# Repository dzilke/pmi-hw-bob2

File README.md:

# PMI backplane BreakOut Board for BreakOut Boards (BoB²)

This pcb is designed for the course PMI (Practical course Microcontroller
and Interface electronics) as a breakout board for right morpho connector
(CN10) of [STM32 Nucleo-64 boards](https://www.st.com/en/evaluation-tools/stm32-nucleo-boards.html). It distributes several signals and bus systems like SPI, I²C, 1-wire, UART and GPIOs. Signal distribution is achieved by pin sockets and headers. The headers can be used to tap signal for anaysis with oscilloscopes or logic analyzers. It also features a 3.3V LDO voltage regulator for power supply and an on board 1-wire DS18B20+ temperature sensor. SPI Chip selects, I²C pull-up resistors and 1-wire parasitic power supply can be enabled over solder bridges.

There are interfaces for GY-291 (ADXL345 accelerometer) and GY-271 (HMC5883L magnet sensor) as well as for our [PMI-ALICE](https://github.com/emtpb/pmi-hw-alice) and [PMI-CARLOS](https://github.com/emtpb/pmi-hw-carlos) breakout boards. Vertical pin sockets are compatible with
[Digilents Pmod](https://digilent.com/reference/pmod/start) interfaces.

# Interactive BOM

An interactive html BOM page with pcb layout and material placement can be found [here](https://emtpb.github.io/pmi-hw-bob2/bom/ibom.html).

# Changelog

## 1.0
* First prototype

## 1.1
* First release

## 1.2
* onewire: Add parasitic power bridge
* pcb: Increase spacing between power section and morpho socket

## 1.3
* Convert project to Kicad 6
* Round pcb corners
* Update linear regulator from MCP1703T-3302E/CB to MCP1703AT-3302E/CB

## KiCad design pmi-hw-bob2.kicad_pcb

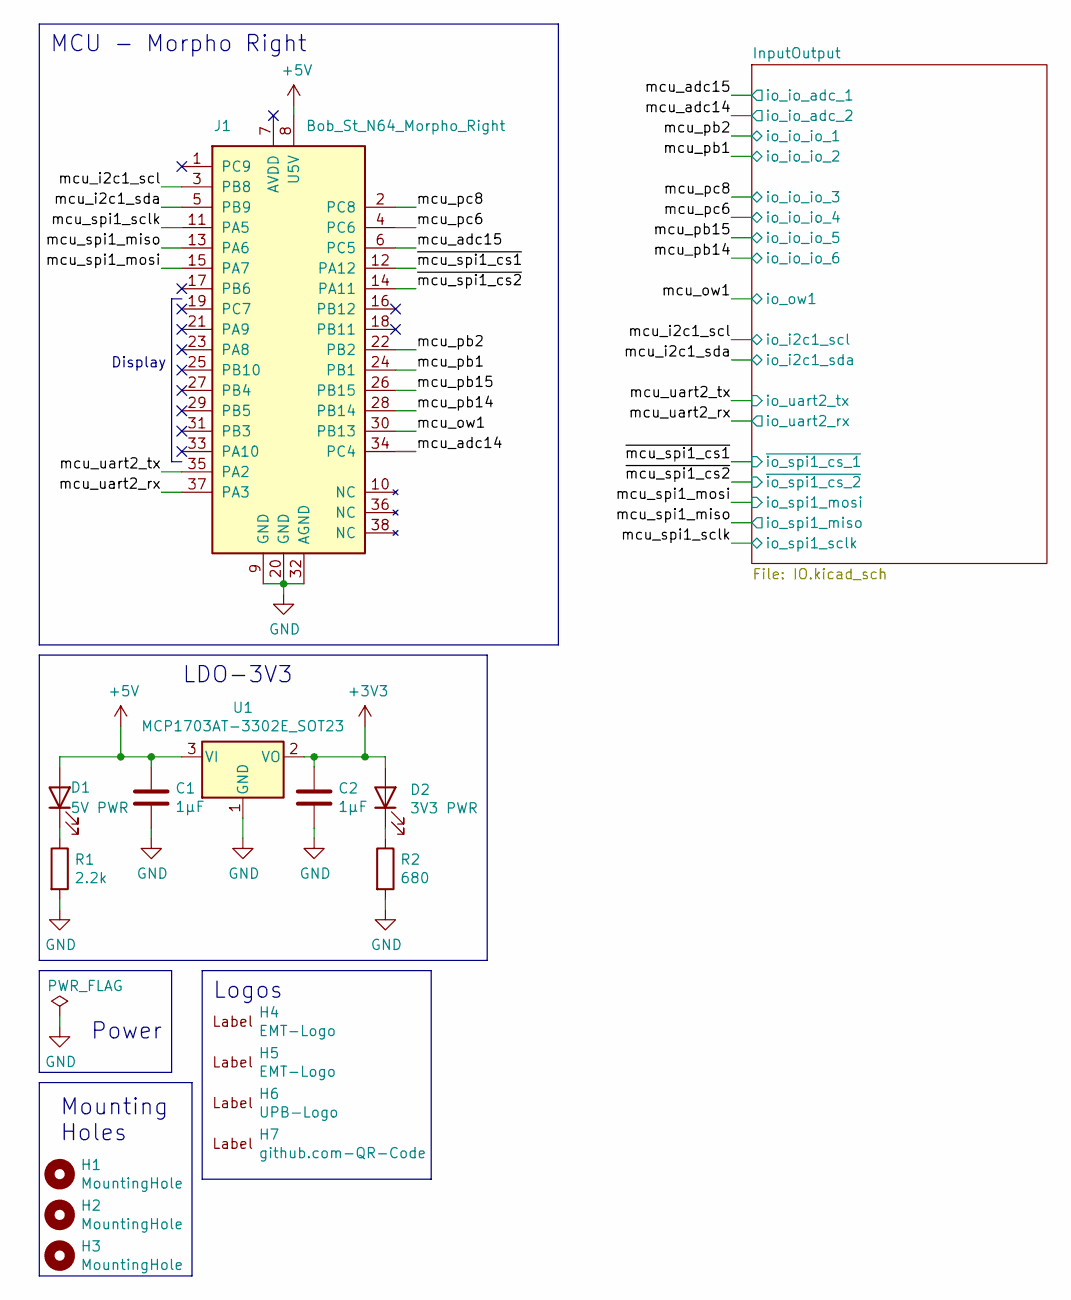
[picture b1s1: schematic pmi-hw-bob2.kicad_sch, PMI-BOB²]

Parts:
C1, C2: 1µF; C_0805_2012Metric
D1: 5V PWR; D_0603_1608Metric; Manufacturer Part No LB L293-M2P1-36-1; Digi-Key No 475-1383-1-ND
D2: 3V3 PWR; D_0603_1608Metric; Manufacturer Part No LB L293-M2P1-36-1; Digi-Key No 475-1383-1-ND
H1, H2, H3: MountingHole; MountingHole_3.2mm_M3
H4: EMT-Logo; EMT-Logo_5.1x2.5mm_Silkscreen
H5: EMT-Logo; EMT-Logo_11.7x5.9mm_Silkscreen
H6: UPB-Logo; UPB-Logo_En_15.9X5.6mm
H7: github.com-QR-Code; github-emtpb-pmi
J1: Bob_St_N64_Morpho_Right; ST_N64_Morpho_Right-emt
R1: 2.2k; R_0603_1608Metric
R2: 680; R_0603_1608Metric
U1: MCP1703AT-3302E_SOT23; SOT-23; Mouser Part No 579-MCP1703AT3302ECB

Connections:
+3V3: C2.1, D2.2 (A), U1.2 (VO); also elsewhere on the board
+5V: C1.1, D1.2 (A), J1.8 (U5V), U1.3 (VI)
/mcu_adc14: J1.34 (PC4); also elsewhere on the board
/mcu_adc15: J1.6 (PC5); also elsewhere on the board
/mcu_i2c1_scl: J1.3 (PB8); also elsewhere on the board
/mcu_i2c1_sda: J1.5 (PB9); also elsewhere on the board
/mcu_ow1: J1.30 (PB13); also elsewhere on the board
/mcu_pb1: J1.24 (PB1); also elsewhere on the board
/mcu_pb2: J1.22 (PB2); also elsewhere on the board
/mcu_pb14: J1.28 (PB14); also elsewhere on the board
/mcu_pb15: J1.26 (PB15); also elsewhere on the board
/mcu_pc6: J1.4 (PC6); also elsewhere on the board
/mcu_pc8: J1.2 (PC8); also elsewhere on the board
/mcu_spi1_miso: J1.13 (PA6); also elsewhere on the board
/mcu_spi1_mosi: J1.15 (PA7); also elsewhere on the board
/mcu_spi1_sclk: J1.11 (PA5); also elsewhere on the board
/mcu_uart2_rx: J1.37 (PA3); also elsewhere on the board
/mcu_uart2_tx: J1.35 (PA2); also elsewhere on the board
/~mcu_spi1_cs1: J1.12 (PA12); also elsewhere on the board
/~mcu_spi1_cs2: J1.14 (PA11); also elsewhere on the board
GND: C1.2, C2.2, J1.9 (GND), J1.20 (GND), J1.32 (AGND), R1.2, R2.2, U1.1 (GND); also elsewhere on the board
unnamed: D1.1 (K), R1.1
unnamed: D2.1 (K), R2.1

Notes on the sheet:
Mounting Holes
LDO-3V3
Logos
Display
MCU - Morpho Right
Power

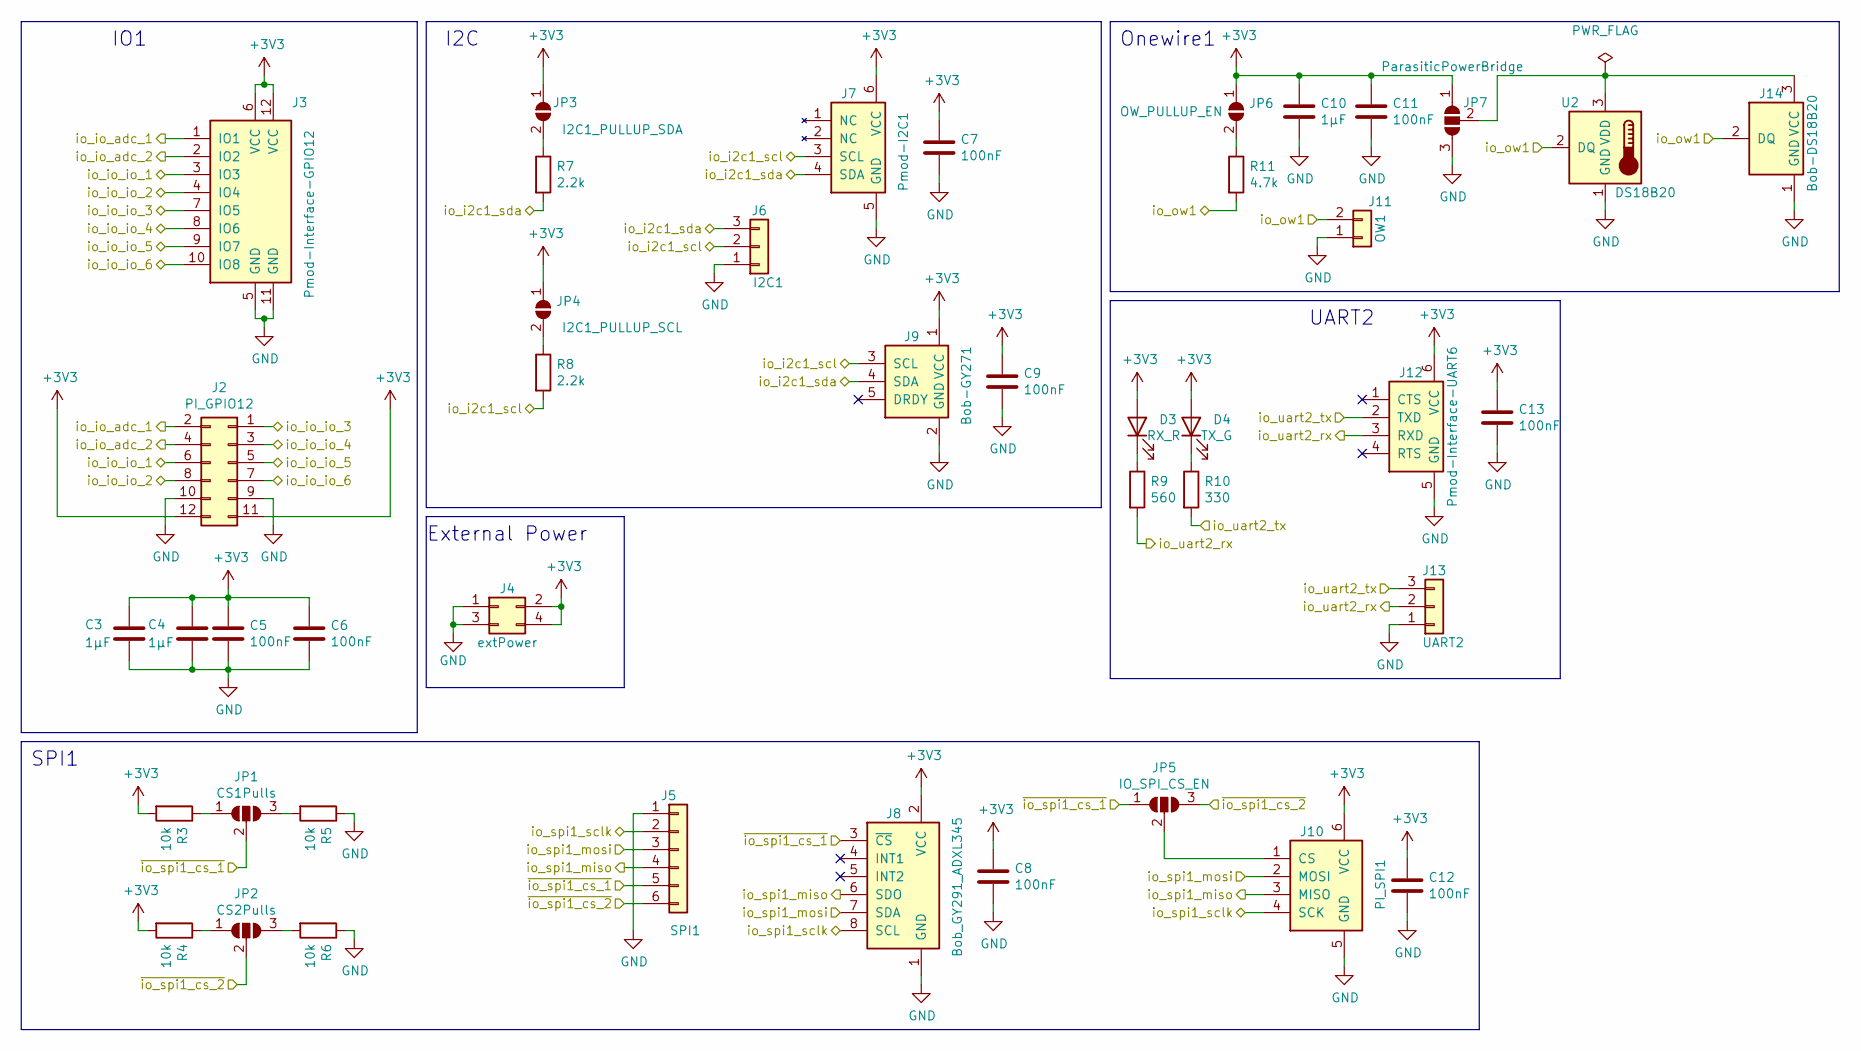
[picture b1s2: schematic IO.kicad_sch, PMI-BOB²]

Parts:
C3, C4, C10: 1µF; C_0805_2012Metric
C5, C6, C7, C8, C9, C11, C12, C13: 100nF; C_0603_1608Metric
D3: RX_R; D_0603_1608Metric; Manufacturer Part No LS L29K-G1H2-1-Z; Digi-Key No 475-3124-1-ND
D4: TX_G; D_0603_1608Metric; Manufacturer Part No LG L29K-F2J1-24-Z; Digi-Key No 475-3118-1-ND
J2: PI_GPIO12; PinHeader_2x06_P2.54mm_Vertical
J3: Pmod-Interface-GPIO12; Pmod_Interface_Female12
J4: extPower; PinHeader_2x02_P2.54mm_Vertical
J5: SPI1; PinHeader_1x06_P2.54mm_Vertical
J6: I2C1; PinHeader_1x03_P2.54mm_Vertical
J7: Pmod-I2C1; Pmod_Interface_Female6
J8: Bob_GY291_ADXL345; PinSocket_1x08_P2.54mm_Vertical
J9: Bob-GY271; PinSocket_1x05_P2.54mm_Vertical
J10: PI_SPI1; Pmod_Interface_Female6
J11: OW1; PinHeader_1x02_P2.54mm_Vertical
J12: Pmod-Interface-UART6; Pmod_Interface_Female6
J13: UART2; PinHeader_1x03_P2.54mm_Vertical
J14: Bob-DS18B20; Bob_DS18B20_Host
JP1: CS1Pulls; SolderJumper-3_P2.0mm_Open_TrianglePad1.0x1.5mm
JP2: CS2Pulls; SolderJumper-3_P2.0mm_Open_TrianglePad1.0x1.5mm
JP3: I2C1_PULLUP_SDA; SolderJumper-2_P1.3mm_Open_TrianglePad1.0x1.5mm
JP4: I2C1_PULLUP_SCL; SolderJumper-2_P1.3mm_Open_TrianglePad1.0x1.5mm
JP5: IO_SPI_CS_EN; SolderJumper-3_P2.0mm_Open_TrianglePad1.0x1.5mm
JP6: OW_PULLUP_EN; SolderJumper-2_P1.3mm_Open_TrianglePad1.0x1.5mm
JP7: ParasiticPowerBridge; SolderJumper-3_P2.0mm_Open_TrianglePad1.0x1.5mm_NumberLabels
R3, R4, R5, R6: 10k; R_0603_1608Metric
R7, R8: 2.2k; R_0603_1608Metric
R9: 560; R_0603_1608Metric
R10: 330; R_0603_1608Metric
R11: 4.7k; R_0603_1608Metric
U2: DS18B20; TO-92_Inline; Mouser Part No 700-DS18B20+

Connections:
+3V3: C3.1, C4.1, C5.1, C6.1, C7.1, C8.1, C9.1, C10.1, C11.1, C12.1, C13.1, D3.2 (A), D4.2 (A), J2.11, J2.12, J3.6 (VCC), J3.12 (VCC), J4.2, J4.4, J7.6 (VCC), J8.2 (VCC), J9.1 (VCC), J10.6 (VCC), J12.6 (VCC), JP3.1 (A), JP4.1 (A), JP6.1 (A), JP7.1 (A), R3.2, R4.2; also elsewhere on the board
/mcu_adc14: J2.4, J3.2 (IO2); also elsewhere on the board
/mcu_adc15: J2.2, J3.1 (IO1); also elsewhere on the board
/mcu_i2c1_scl: J6.2, J7.3 (SCL), J9.3 (SCL), R8.2; also elsewhere on the board
/mcu_i2c1_sda: J6.3, J7.4 (SDA), J9.4 (SDA), R7.2; also elsewhere on the board
/mcu_ow1: J11.2, J14.2 (DQ), R11.2, U2.2 (DQ); also elsewhere on the board
/mcu_pb1: J2.8, J3.4 (IO4); also elsewhere on the board
/mcu_pb2: J2.6, J3.3 (IO3); also elsewhere on the board
/mcu_pb14: J2.7, J3.10 (IO8); also elsewhere on the board
/mcu_pb15: J2.5, J3.9 (IO7); also elsewhere on the board
/mcu_pc6: J2.3, J3.8 (IO6); also elsewhere on the board
/mcu_pc8: J2.1, J3.7 (IO5); also elsewhere on the board
/mcu_spi1_miso: J5.4, J8.6 (SDO), J10.3 (MISO); also elsewhere on the board
/mcu_spi1_mosi: J5.3, J8.7 (SDA), J10.2 (MOSI); also elsewhere on the board
/mcu_spi1_sclk: J5.2, J8.8 (SCL), J10.4 (SCK); also elsewhere on the board
/mcu_uart2_rx: J12.3 (RXD), J13.2, R9.2; also elsewhere on the board
/mcu_uart2_tx: J12.2 (TXD), J13.3, R10.2; also elsewhere on the board
/~mcu_spi1_cs1: J5.5, J8.3 (~CS), JP1.2 (C), JP5.1 (A); also elsewhere on the board
/~mcu_spi1_cs2: J5.6, JP2.2 (C), JP5.3 (B); also elsewhere on the board
GND: C3.2, C4.2, C5.2, C6.2, C7.2, C8.2, C9.2, C10.2, C11.2, C12.2, C13.2, J2.9, J2.10, J3.5 (GND), J3.11 (GND), J4.1, J4.3, J5.1, J6.1, J7.5 (GND), J8.1 (GND), J9.2 (GND), J10.5 (GND), J11.1, J12.5 (GND), J13.1, J14.1 (GND), JP7.3 (B), R5.1, R6.1, U2.1 (GND); also elsewhere on the board
unnamed: D3.1 (K), R9.1
unnamed: D4.1 (K), R10.1
unnamed: J10.1 (CS), JP5.2 (C)
unnamed: J14.3 (VCC), JP7.2 (C), U2.3 (VDD)
unnamed: JP1.1 (A), R3.1
unnamed: JP1.3 (B), R5.2
unnamed: JP2.1 (A), R4.1
unnamed: JP2.3 (B), R6.2
unnamed: JP3.2 (B), R7.1
unnamed: JP4.2 (B), R8.1
unnamed: JP6.2 (B), R11.1

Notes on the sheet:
UART2
External Power
Onewire1
SPI1
I2C
IO1

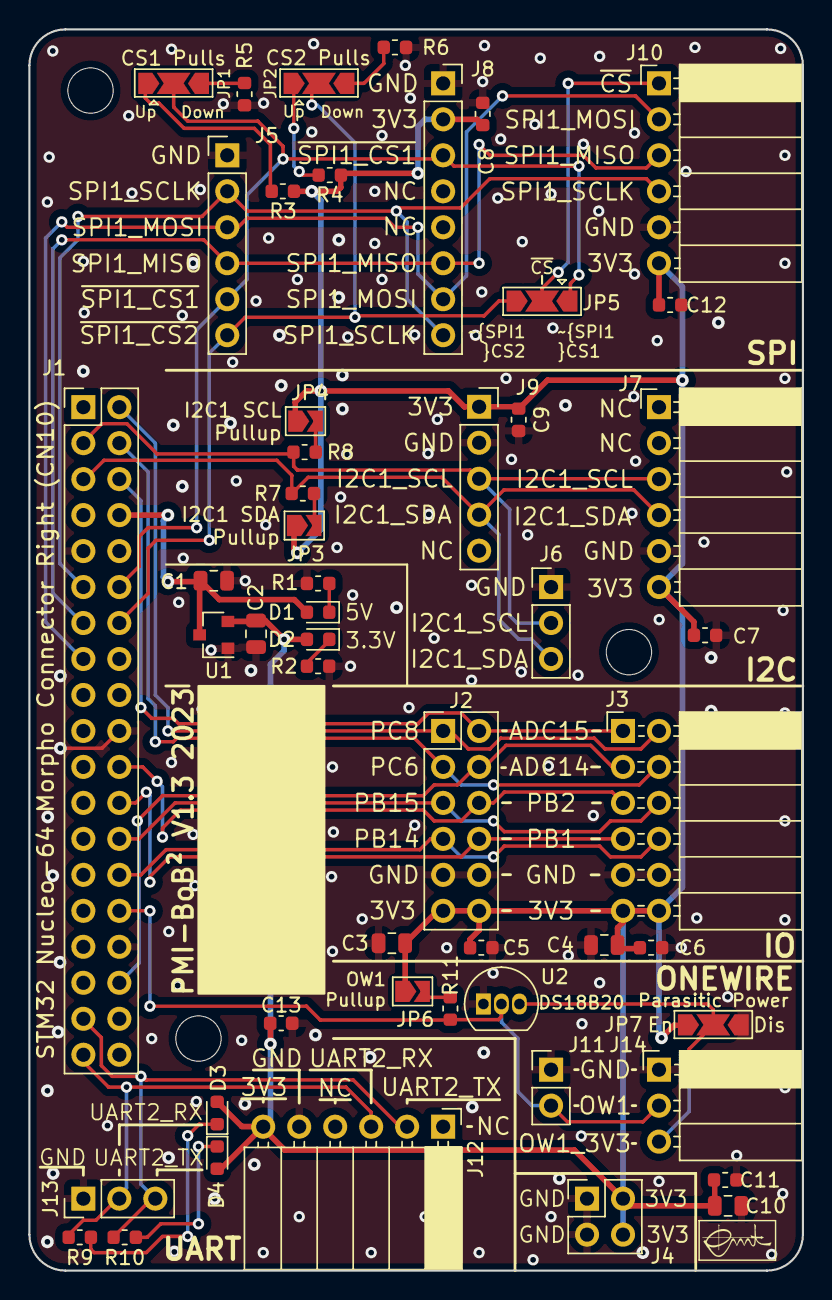
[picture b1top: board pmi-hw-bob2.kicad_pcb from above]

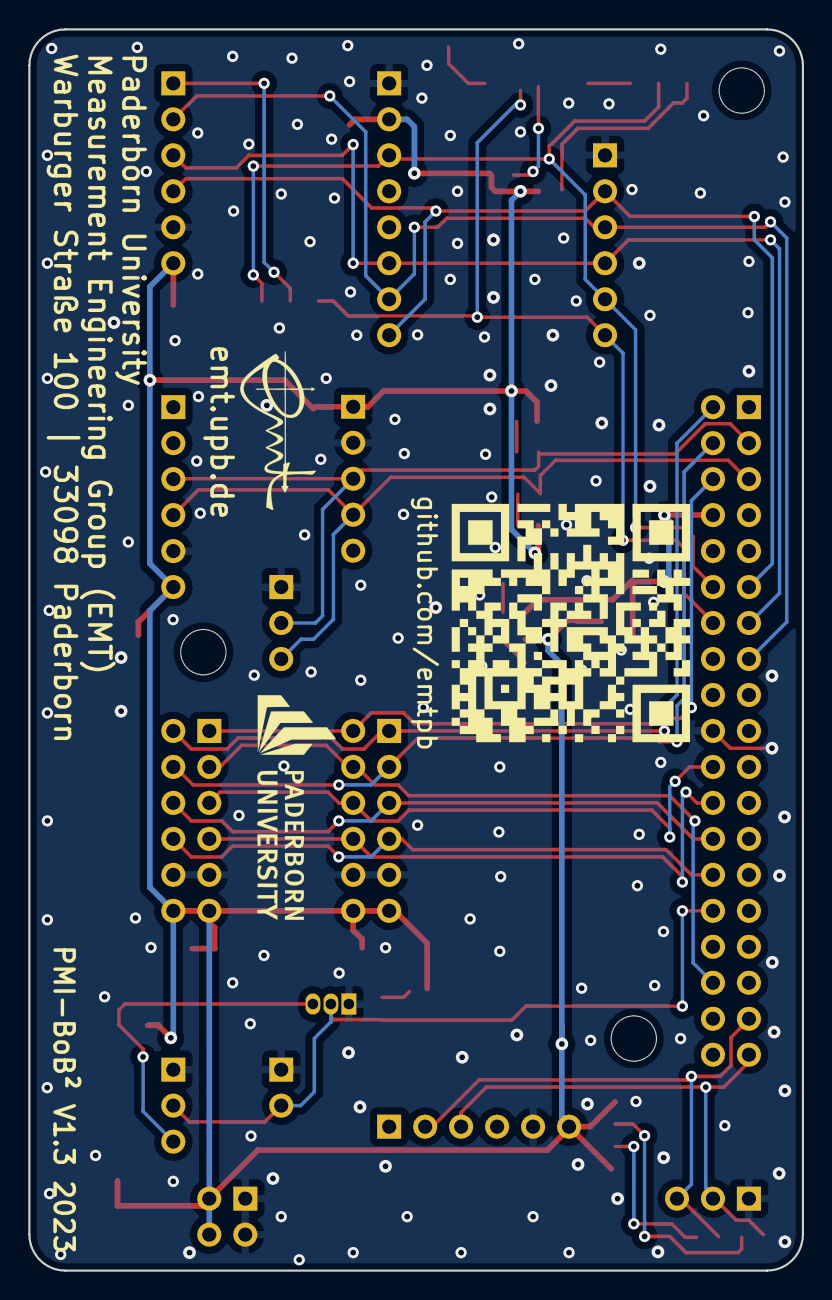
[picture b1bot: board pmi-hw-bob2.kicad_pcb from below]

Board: 2 copper layers, 54.6 x 87.6 mm, 58 parts (3 on the bottom side), 34 nets.

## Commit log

2021-12-23 Initial revision
2022-01-11 Fix empty IO.sch file
2022-01-11 Bump to version 1.2
2023-02-21 Bump to version 1.3
2025-05-22 Add interactive BOM link
